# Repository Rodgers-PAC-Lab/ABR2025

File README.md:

# ABR2025

## Introduction

This repository contains code to implement the ABR measuring system described
in Gargiullo et al, as well as the analysis scripts needed to replicate the 
figures in that paper.
Preprint: https://www.biorxiv.org/content/10.64898/2025.12.17.694771v1

The repository is structured as follows:
- `./` - The toplevel directory, containing this README file
- `./designs` - Design files, bill of materials, and other information about 
physically building the system.
- `./src` - source code for analysis and GUI. Import like `import opensabr`
- `./src/gui` - A Python module for running the graphical user interface (GUI) 
to take ABR data. It can be imported like `import opensabr.gui`. This code is 
run on a desktop PC connected to the ABR measuring system hardware.
- `./scripts` - A folder of demo scripts that generate the figures in the
paper, using data that we collected and have shared on Zenodo. These scripts 
are meant to be run one at a time, not imported and called by other scripts. 

## Requirements

We used Python 3.11. Newer versions may also work but we did not test them.

requirements-lock.txt includes the exact versions we used

For the analysis scripts (but not the GUI), the following repository is 
required. It should be on your PYTHONPATH so that it can be imported using
the syntax `import my`.
- `git clone git@github.com:Rodgers-PAC-Lab/my.git`

TODO: only my.plot is needed, bring minimal into this repo

## Instructions

To build the hardware, refer to the file `./designs/README`. 

To run the GUI and measure ABR, refer to the file `./gui/README`.

To run the analysis scripts and regenerate the figures included in the paper,
refer to the file `./scripts/README`.

## Overall installation instructions
These instructions walk you through the installation of OpenSABR, our fork
of ABRA, and our fork of ABRpresto in three different conda environments.
If you only want to run OpenSABR, you can skip the other two environments --
they are only used to provide a point of comparison in the paper. 

We clone repositories that are installed using a method like `pip install`
into a directory called `~/dev/installed`. We clone repositories that are 
not installable, but need to be imported, into a directory called `~/dev`.
ABRA is the only one that must be cloned into `~/dev`.
This is because it can cause errors to mix these two kinds of repositories.
`~/dev` must be on the PYTHONPATH for this to work. 

For ABRA, we recommend the CPU packages, there is no need for GPU.

The three conda environments share data written to disk in the parquet format.

## Installing OpenSABR
# Clone repo
cd ~/installed
git clone git@github.com:Rodgers-PAC-Lab/OpenSABR
cd OpenSABR

# --- Install: pick ONE of Option A or Option B ---

# Option A: Typical install (no version pins)
conda create -n opensabr -c conda-forge python=3.11 pip ipython
conda activate opensabr
conda install -c conda-forge numpy scipy pandas matplotlib tqdm pyqt pyqtgraph pyserial pyarrow seaborn
pip install -e . --no-deps

# Option B: Reproducible install from lock (linux-64 only)
conda create -n opensabr --file opensabr-conda-lock.txt
conda activate opensabr
pip install -e . --no-deps

## Installing ABRpresto
# Clone repo
cd ~/installed 
git clone git@github.com:Rodgers-PAC-Lab/ABRpresto # our fork
cd ABRpresto
git checkout dev # our branch with fixes

# --- Install: pick ONE of Option A or Option B ---

# Option A: Typical install (no version pins)
conda create -n abrpresto -c conda-forge python=3.11 ipython pip
conda activate abrpresto
conda install -c conda-forge numpy scipy pandas matplotlib setuptools_scm pyarrow tqdm
pip install -e . --no-deps

# Option B: Reproducible install from lock (linux-64 only)
conda create -n abrpresto --file abrpresto-conda-lock.txt
conda activate abrpresto
pip install -e . --no-deps

## Installing ABRA
# Clone repo (must be under ~/dev or some location on PYTHONPATH)
cd ~/dev
git clone git@github.com:Rodgers-PAC-Lab/abranalysis # our fork
cd abranalysis
git checkout dev # our branch with fixes

# --- Install: pick ONE of Option A or Option B ---
# ABRA cannot be pip-installed; it is imported via PYTHONPATH in both options.

# Option A: Typical install (no version pins)
conda create -n abra -c conda-forge python=3.11 ipython pip
conda activate abra
conda install -c conda-forge numpy scipy pandas scikit-learn pytorch=*=cpu* keras tensorflow streamlit easydict "altair<5" pyarrow matplotlib tqdm
conda env config vars set PYTHONPATH=$HOME/dev
conda deactivate && conda activate abra   # reload so PYTHONPATH takes effect

# Option B: Reproducible install from lock (linux-64 only)
conda create -n abra --file abra-conda-lock.txt
conda activate abra
conda env config vars set PYTHONPATH=$HOME/dev
conda deactivate && conda activate abra   # reload so PYTHONPATH takes effect

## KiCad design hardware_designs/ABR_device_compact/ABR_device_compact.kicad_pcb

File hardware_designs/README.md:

# ABR2025 - hardware designs

## Introduction 

This folder contains the designs needed to build the hardware for the 
ABR measuring system described in Gargiullo 2025.

It contains the following subfolders:
- bill_of_materials.xlsx: Bill of Materials for all required parts
- interface_pcb/: PCB design files for the "interface PCB" that houses the
Teensy and connects to the other boards
- teensy/: Files for the code that runs on the Teensy

### Bill of Materials

This is an Excel file of all required components. You will also need standard
electronics equipment for soldering, etc.

### Interface PCB

This PCB was designed in Eagle. The original design files are located in the
`eagle` subdirectory and can be opened in the Eagle software. You only need to 
do this if you want to edit the PCB.

If you just want to print the PCB, use the files in the `gerbers` subdirectory.
These are the standard manufacturing format that all PCB printing companies use.
We used OSH Park to print the PCB.

After you receive the PCB, you will need to populate a few components. Details
are available in the "Supplemental Material", which also explains how to 
physically assemble all components.

### Teensy files

This is the software that runs on the Teensy. The software controls the 
ADS1299, and it also interfaces with the desktop computer running the GUI
(see `../gui/README`). Flash the files included here on the Teensy.

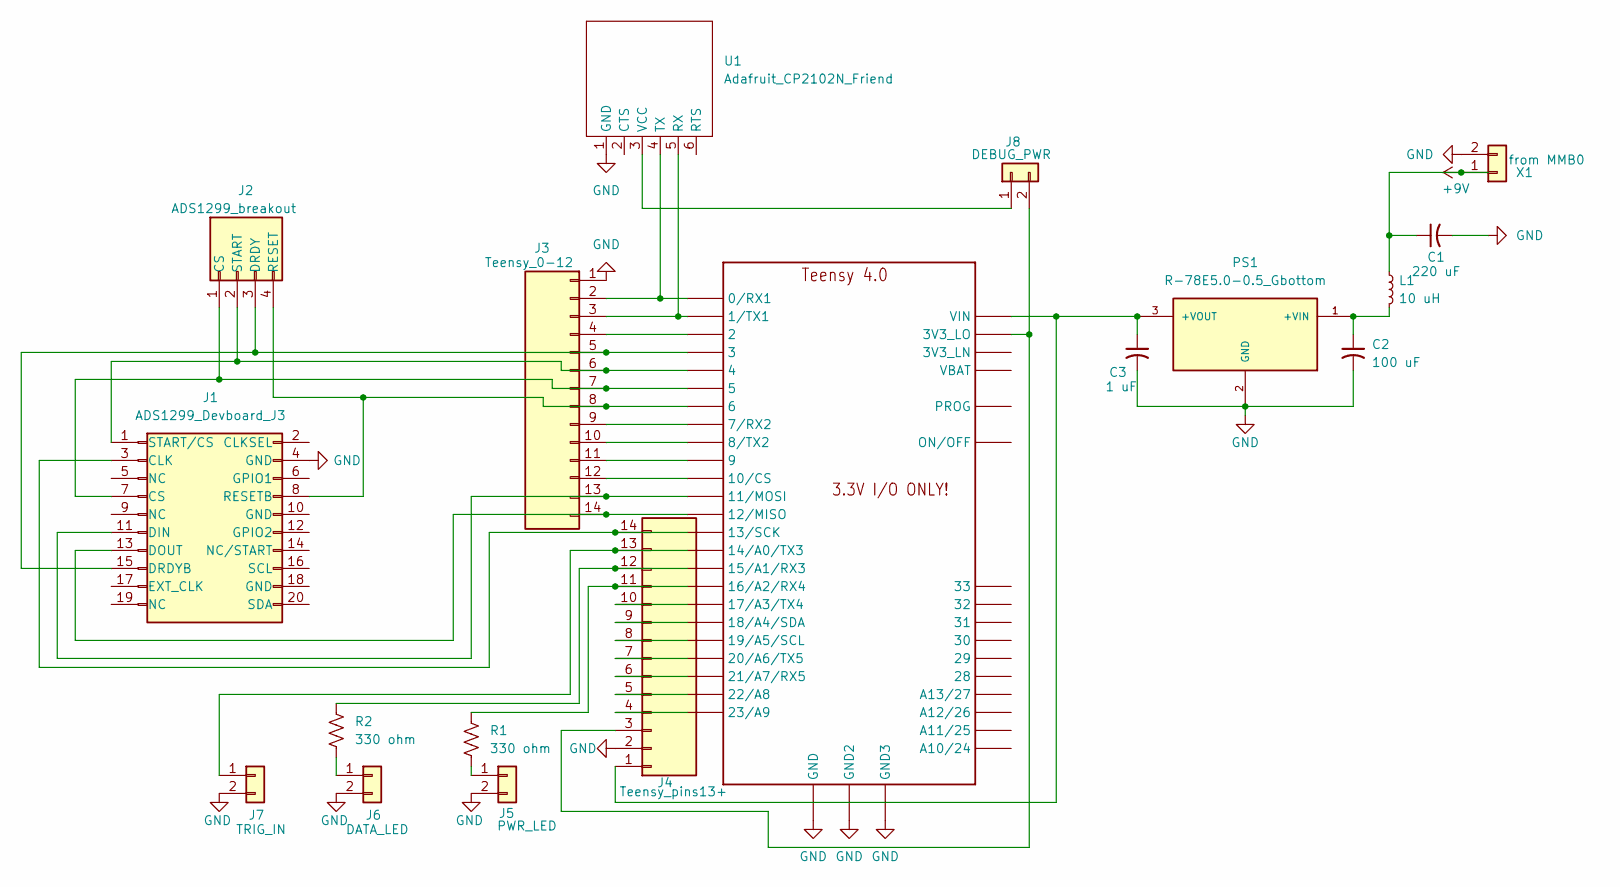
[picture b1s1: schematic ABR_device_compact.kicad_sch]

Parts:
1: TEENSY_4.0_WITH_24-33
C1: 220 uF; CP_Radial_D10.0mm_P5.00mm
C2: 100 uF; CP_Radial_D8.0mm_P3.80mm
C3: 1 uF; CP_Radial_D7.5mm_P2.50mm
J1: ADS1299_Devboard_J3; IDC-Header_2x10_P2.54mm_Vertical
J2: ADS1299_breakout; PinSocket_1x04_P2.54mm_Vertical
J3: Teensy_0-12; PinHeader_1x14_P2.54mm_Vertical
J4: Teensy_pins13+; PinHeader_1x14_P2.54mm_Vertical
J5: PWR_LED; PinHeader_1x02_P2.54mm_Vertical
J6: DATA_LED; PinHeader_1x02_P2.54mm_Vertical
J7: TRIG_IN; PinHeader_1x02_P2.54mm_Vertical
J8: DEBUG_PWR; PinHeader_1x02_P2.54mm_Vertical
L1: 10 uH; L_Axial_L9.5mm_D4.0mm_P15.24mm_Horizontal_Fastron_SMCC
PS1: R-78E5.0-0.5_Gbottom; CONV_R-78E5.0-0.5; PARTREV v4
R1, R2: 330 ohm; R_Axial_DIN0207_L6.3mm_D2.5mm_P10.16mm_Horizontal
U1: Adafruit_CP2102N_Friend
X1: from MMB0; JST_XH_B2B-XH-A_1x02_P2.50mm_Vertical

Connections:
+9V: C1.1, L1.1, X1.1
GND: 1.GND, 1.GND2, 1.GND3, C1.2, C2.2, C3.2, J1.4 (GND), J3.1, J4.2, J5.2, J6.2, J7.2, PS1.2 (GND), U1.1 (GND), X1.2
unnamed: 1.0/RX (0/RX1), J3.2, U1.4 (TX)
unnamed: 1.1/TX (1/TX1), J3.3, U1.5 (RX)
unnamed: 1.7 (7/RX2), J3.9
unnamed: 1.8 (8/TX2), J3.10
unnamed: 1.14/A0 (14/A0/TX3), J4.13, J7.1
unnamed: 1.15/A1 (15/A1/RX3), J4.12, R2.1
unnamed: 1.16/A2 (16/A2/RX4), J4.11, R1.1
unnamed: 1.17/A3 (17/A3/TX4), J4.10
unnamed: 1.20/A6 (20/A6/TX5), J4.7
unnamed: 1.21/A7 (21/A7/RX5), J4.6
unnamed: 1.13/SCK, J1.3 (CLK), J4.14
unnamed: 1.5, J1.7 (CS), J2.1 (CS), J3.7
unnamed: 1.11/MOSI, J1.11 (DIN), J3.13
unnamed: 1.12/MISO, J1.13 (DOUT), J3.14
unnamed: 1.3, J1.15 (DRDYB), J2.3 (DRDY), J3.5
unnamed: 1.6, J1.8 (RESETB), J2.4 (RESET), J3.8
unnamed: 1.4, J1.1 (START/CS), J2.2 (START), J3.6
unnamed: 1.2, J3.4
unnamed: 1.9, J3.11
unnamed: 1.10/CS, J3.12
unnamed: 1.VIN, C3.1, J4.1, PS1.3 (+VOUT)
unnamed: 1.3V3_LO, J4.3, J8.2
unnamed: 1.23/A9, J4.4
unnamed: 1.22/A8, J4.5
unnamed: 1.19/A5/SCL, J4.8
unnamed: 1.18/A4/SDA, J4.9
unnamed: J5.1, R1.2
unnamed: J6.1, R2.2
unnamed: J8.1, U1.3 (VCC)
unnamed: C2.1, L1.2, PS1.1 (+VIN)

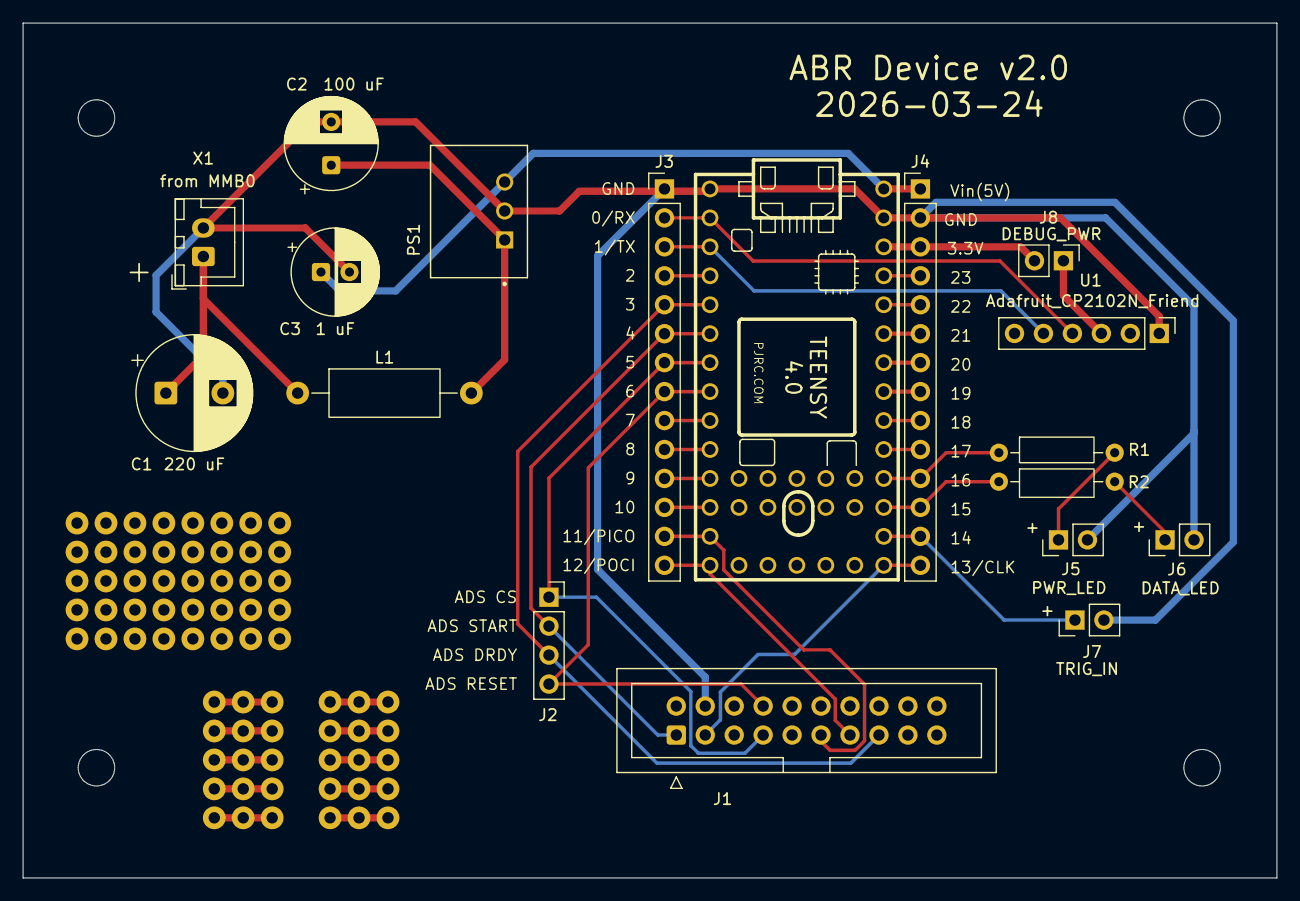
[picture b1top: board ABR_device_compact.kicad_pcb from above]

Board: 2 copper layers, 110.0 x 75.0 mm, 87 parts (0 on the bottom side), 32 nets.

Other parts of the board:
2, 3, 4, 5, 6, 7, 8, 9, 9#2, 10, 11, 12, 13, 14, 15, 16, 17, 17#2, 18, 19, 20, 21, 22, 23, 24, 25, 25#2, 26, 27, 28, 29, 30, 31, 32, 33, 34, 35, 36, 37, 38, 39, 40, 41, 41#2, 42, 43, 44, 45, 46, 47, 48, 49, 57, 58, 59, 60, 61, 62, 63, 64, 65, 66, 67, 68, 69, 70, 71, 72, 73: (no value)

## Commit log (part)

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2025-07-21 Starting to copy stuff over to the new repo. Also changed the get_filepaths() function to take a json with filepaths as discussed.
2025-07-22 deleting abr subfolder
2025-07-22 move analysis scripts into main directory
2025-07-22 add metadata mouse_info.csv
2025-07-22 explain how to set up filepaths.json
2025-07-22 add filepaths.json to gitignore
2025-07-22 newline added
2025-07-22 load from filepaths and mouse_data.csv in current directory
2025-07-22 import abr from paclab
2025-07-22 fix directory names
2025-07-22 Possible solution to the whole two mouse_info.csv thing. Add cohort name to the filename and have both in there, use RUN_STEPS1-2 to do the first two steps to both cohorts. You'll want to run Step3 i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
2025-07-23 CR versions to avoid merge conflict
2025-07-24 remove slow code and update filename
2025-07-24 doc and remove ion
2025-07-24 doc; remove ion; update filepaths
2025-07-24 add Rowan's stats_pickle_v2
2025-07-24 update filepaths and doc
2025-07-24 adding rowan's Grand_averages
2025-07-24 update filepaths
2025-07-24 Changes we made together
2025-07-24 Forgot to add these earlier
2025-07-25 doc and spacing
2025-07-25 split Step2 into Step2 and Step2b
2025-07-25 spacing; doc; save data
2025-07-25 update - new way of parsing, new types of csv
2025-07-25 rename
2025-07-25 remove include drop (done in Step1 now)
2025-07-25 new csv
2025-07-25 move savefils
2025-07-28 move thresh to Step2c; add figs for Step2b
2025-07-28 stub for EKG
2025-07-28 PSD plotting script
2025-07-29 EKG plots
2025-08-10 remove RUN_STEPS1-2
2025-08-11 plots and update for step2b
2025-08-12 fix the noise plot
2025-08-12 deleting old file; renaming grand_averages to step3a
2025-08-12 psd plot
2025-08-12 correlate
2025-08-13 remove
2025-08-13 remove old files
2025-08-15 remove fig4_plots
2025-08-18 remove Plot_thresholds
2025-08-18 add metadata to subdirectory
2025-08-18 move metadata to subfolder
2025-08-18 savefig
2025-08-19 update doc about which scripts make which plots
2025-08-20 Metadata csvs are in a subfolder, changed the hard coded file path to reflect that.
2025-08-21 Renamed scripts
2025-08-23 add 250725_cohort to metadata
2025-08-23 make figures dir
2025-08-23 fix dB; check for glitches on load
2025-08-23 store figs in figures
2025-08-23 fix loudest db and store figs in figures
2025-08-23 another bad session
2025-08-23 show
2025-08-24 error bars for plot_abr_rms
2025-08-24 store all figures in figures/
2025-08-24 remove torn data
2025-08-24 doc; store Pxx; correct stats
2025-08-24 fix aggregation
2025-08-24 fix loudest_db; update
2025-08-24 handle missing mice
2025-08-24 remove breakpoint
2025-08-24 drop more torn sessions
2025-08-24 properly label channels
2025-08-24 update figures
2025-09-01 stats
2025-10-28 indenting
2025-10-28 comment
2025-10-29 also get PSDs
2025-10-29 just plot PSD
2025-10-29 plot raw data script
2025-10-30 also get EKG
2025-10-30 adjust for EKG loaded in Step2a1 now
2025-11-02 todo
2025-11-23 move everything for the paper into scripts
2025-11-23 Revert "move everything for the paper into scripts"
    This reverts commit 5d96bef88c4e92456698c6ead33062e73cff930a.
2025-11-23 Reapply "move everything for the paper into scripts"
    This reverts commit 08afd14b9bcfc3f12d41770581b7fc40990b161a.
2025-11-23 add gui files
2025-11-23 add loading and signal processing
2025-11-23 make it a module
2025-11-23 ignore scripts/figures
2025-11-23 do HL_type right away; replace module name; mice are now dropped upstream
2025-11-23 fix module name; slice more data
2025-11-23 remove imports, fix echoing
2025-11-23 remove imports; fix modulename
2025-11-23 return to typical window size
2025-11-23 replace module names
2025-11-23 fix font
2025-11-23 save aggregated versions in Step2b
2025-11-23 module fix; use none instead of nan; some stuff done upstream
2025-11-23 mice now dropped upstream
2025-11-23 fix bug
2025-11-23 remove dup code now upstream
2025-11-23 move aggregation upstream and always do first experiment
2025-11-23 remove doc
2025-11-26 update calibration
2025-11-26 code to check psd by sex and HL
2025-11-26 adjust for SPL
2025-11-26 fix SPL; stats on threshold; stub code on rms comparisons
2025-11-26 removing old code
2025-11-26 doc on stats; fix mu
2025-12-06 ignore pycache
2025-12-07 fix missing join on trial_counts
2025-12-07 fix colorbar and update doc
2025-12-07 fix colorbar an dyticks
2025-12-09 update peak height analysis
2025-12-11 dump overall N
2025-12-11 more stats
2025-12-12 PCB files
2025-12-12 removing old style paclab.abr imports
2025-12-12 bring in the old functions for identifying onsets
2025-12-12 move psd to signal_processing
2025-12-13 rewrite to generate CSV files and to use sliced dataset
2025-12-13 use new CSV metadata and new sliced dataset
2025-12-14 fix ticks
2025-12-14 move get_ABR_data_paths to paclab.abr_misc
2025-12-14 move old functios to abr_misc
2025-12-14 doc on zip
2025-12-14 READMEs
2025-12-14 adding teensy file
2025-12-14 updating readme
2025-12-15 moved teensy and renamed designs
2025-12-15 Added bill of materials
2025-12-15 Add download link for ABR data in README
2025-12-15 Adding teensy .cpp and .h files
2025-12-18 remove now unnecessary Step1
2026-03-18 fix legend order
2026-06-24 create output dir
2026-06-24 missing space
2026-06-24 begin inverting channels; remove old commented code
2026-06-24 add PLOT_GROWTH_FUNCTIONS
2026-06-24 invert channels
2026-06-29 align yaxis across plots
2026-06-30 invert
2026-06-30 add plot vs age
